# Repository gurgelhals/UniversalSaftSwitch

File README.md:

UniversalSaftSwitch
===========

UniversalSaftSwitch - powers on/off devices using the RS-485 bus

Fuses:
-U lfuse:w:0xde:m -U hfuse:w:0xdf:m -U efuse:w:0xff:m 

project page: https://www.binary-kitchen.de/wiki/doku.php?id=projekte:hausautomatisierung:uss

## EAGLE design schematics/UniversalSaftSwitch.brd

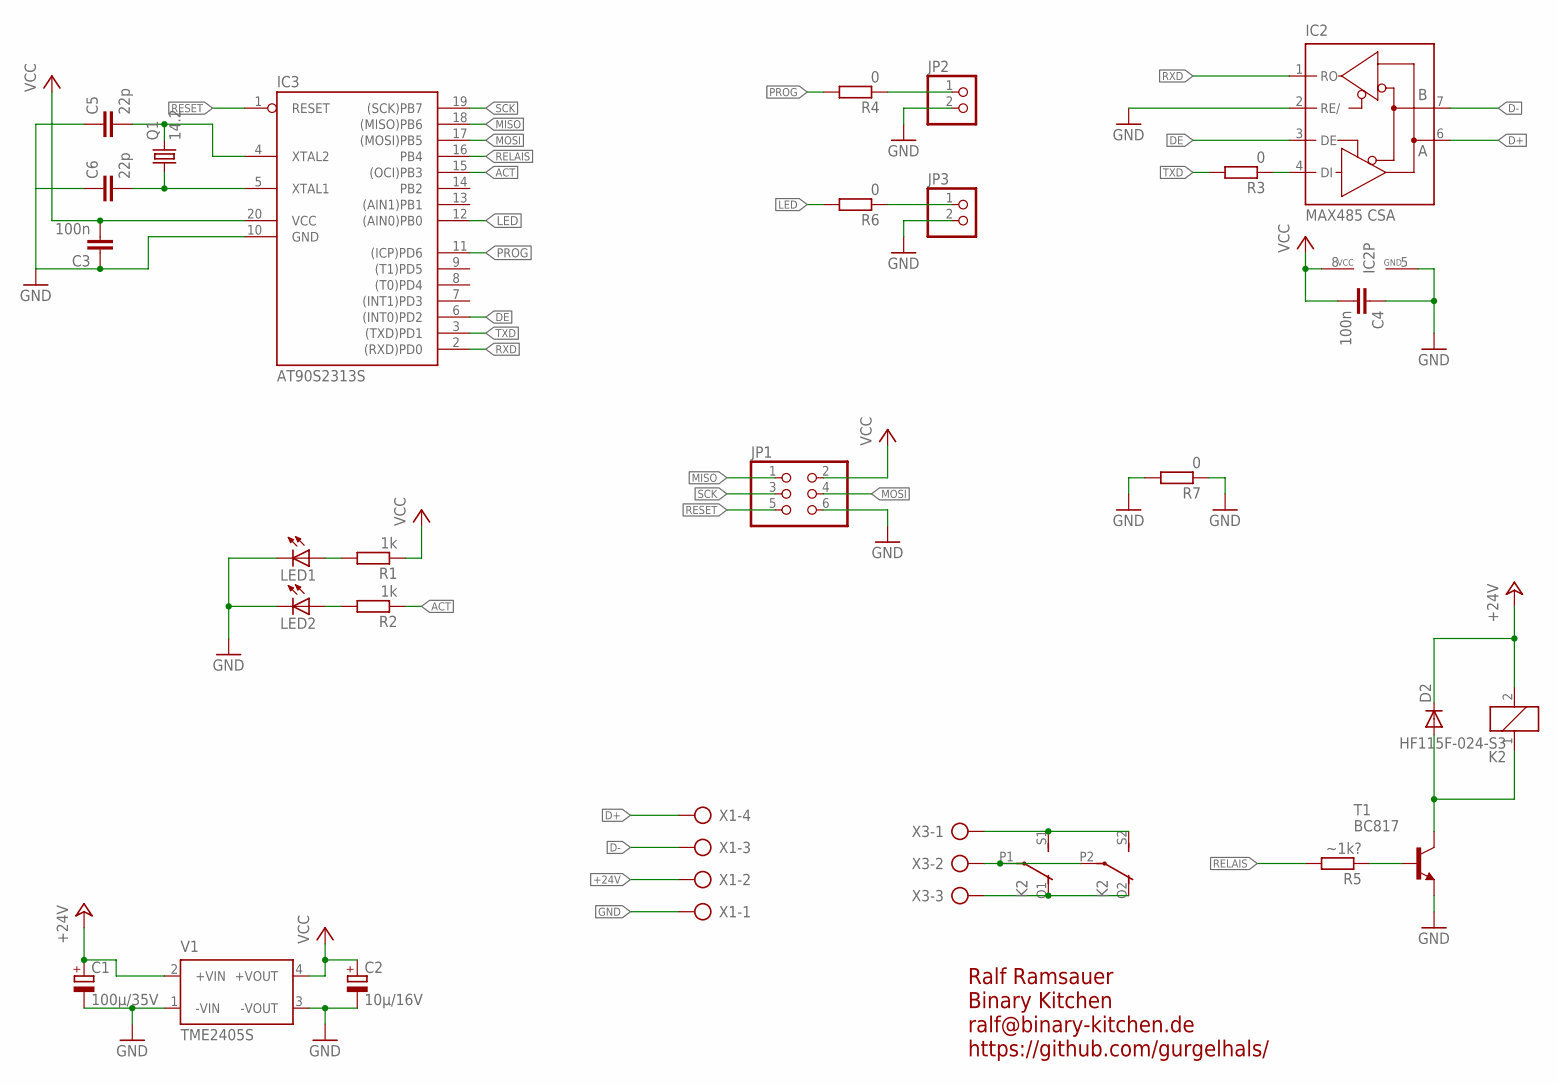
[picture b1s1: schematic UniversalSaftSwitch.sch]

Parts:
C1: 100µ/35V; E3,5-8
C2: 10µ/16V; E2-4
C3, C4: 100n; C0805K
C5, C6: 22p; C0805K
D2: DIODE-MINIMELF; MINIMELF
IC2: MAX485 CSA; SO08
IC3: AT90S2313S; SO20L
JP1: PINHD-2X3; 2X03
JP2, JP3: PINHD-1X2; 1X02
K2: HF115F-024-S3; F4052
LED1, LED2: LED3MM
Q1: 14.2; HC49U-V
R1, R2: 1k; M0805
R3, R4, R6, R7: 0; M0805
R5: ~1k?; M0805
T1: BC817; SOT23-BEC
V1: TME2405S; TME-24V
X1: AK500/4
X3: AK500/3

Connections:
+24V: C1.+, D2.C, K2.2, V1.2 (+VIN), X1.2
ACT: IC3.15 ((OCI)PB3), R2.1
D+: IC2.6 (A), X1.4
D-: IC2.7 (B), X1.3
DE: IC2.3 (DE), IC3.6 ((INT0)PD2)
GND: C1.-, C2.-, C3.1, C4.1, C5.1, C6.1, IC2.2 (RE/), IC2.5 (GND), IC3.10 (GND), JP1.6, JP2.2, JP3.2, LED1.K (C), LED2.K (C), R7.1, R7.2, T1.E, V1.1 (-VIN), V1.3 (-VOUT), X1.1
LED: IC3.12 ((AIN0)PB0), R6.2
MISO: IC3.18 ((MISO)PB6), JP1.1
MOSI: IC3.17 ((MOSI)PB5), JP1.4
unnamed: IC2.4 (DI), R3.1
unnamed: LED1.A, R1.2
unnamed: LED2.A, R2.2
unnamed: K2.S1 (S), K2.S2 (S), X3.1
unnamed: K2.O1 (O), K2.O2 (O), X3.3
unnamed: K2.P1, K2.P2, X3.2
unnamed: C5.2, IC3.4 (XTAL2), Q1.2
unnamed: D2.A, K2.1, T1.C
unnamed: R5.1, T1.B
unnamed: C6.2, IC3.5 (XTAL1), Q1.1
unnamed: JP2.1, R4.1
unnamed: JP3.1, R6.1
PROG: IC3.11 ((ICP)PD6), R4.2
RELAIS: IC3.16 (PB4), R5.2
RESET: IC3.1 (RESET), JP1.5
RXD: IC2.1 (RO), IC3.2 ((RXD)PD0)
SCK: IC3.19 ((SCK)PB7), JP1.3
TXD: IC3.3 ((TXD)PD1), R3.2
VCC: C2.+, C3.2, C4.2, IC2.8 (VCC), IC3.20 (VCC), JP1.2, R1.1, V1.4 (+VOUT)

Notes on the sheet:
Ralf Ramsauer Binary Kitchen ralf@binary-kitchen.de https://github.com/gurgelhals/

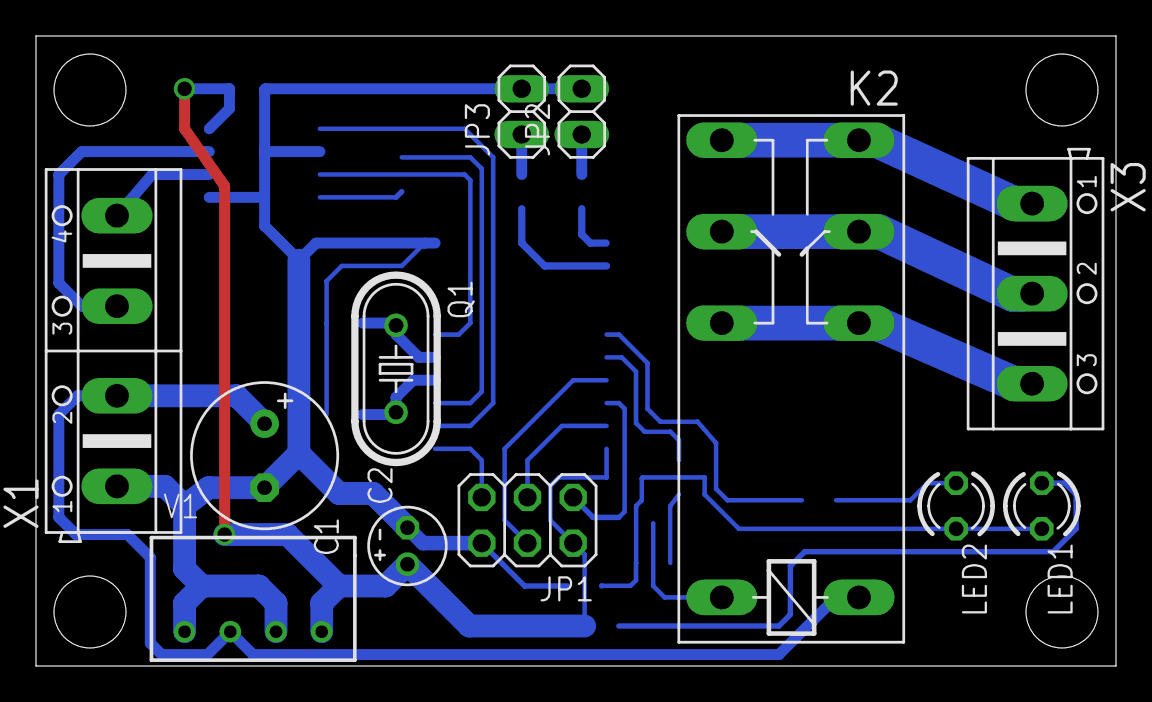
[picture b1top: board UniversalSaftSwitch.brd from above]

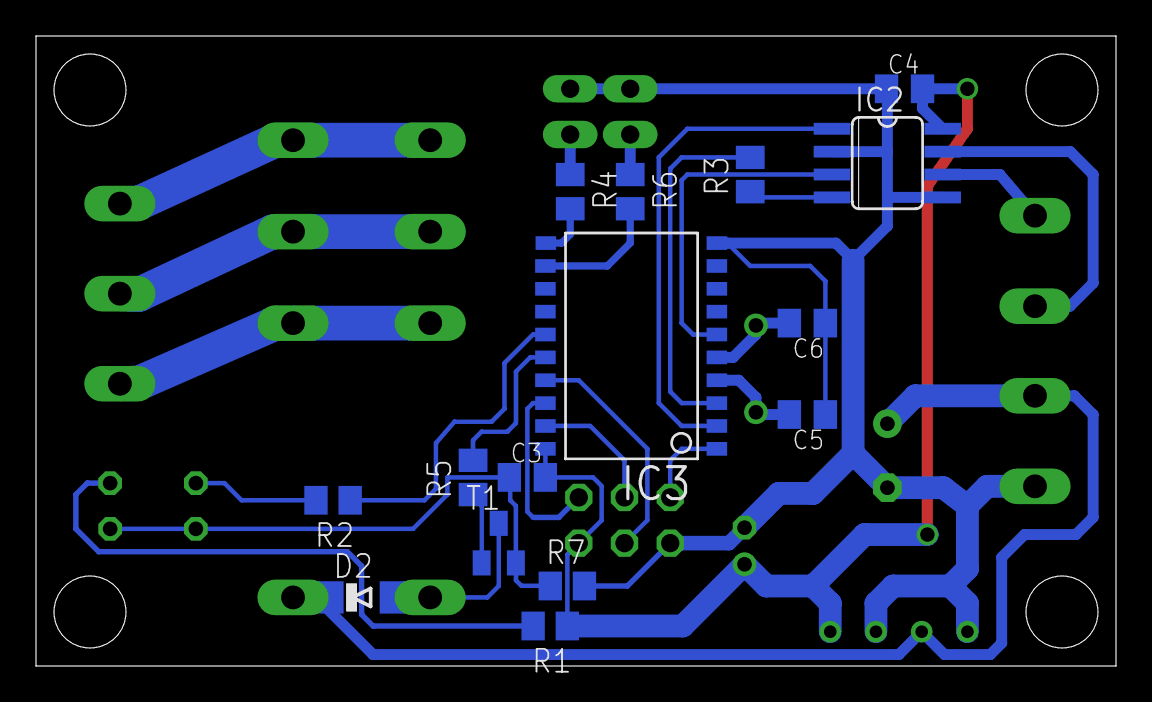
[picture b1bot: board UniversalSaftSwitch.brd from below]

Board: 2 copper layers, 60.0 x 35.0 mm, 27 parts (15 on the bottom side), 28 nets.

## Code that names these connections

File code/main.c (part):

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#include <avr/sleep.h>
#include <string.h>

#define ACT_ON (PORTB |= (1<<PB3))
#define ACT_OFF (PORTB &= ~(1<<PB3))

#define REL_ON (PORTB |= (1<<PB4))
#define REL_OFF (PORTB &= ~(1<<PB4))

#define PROG_ON (!(PIND & (1<<PD6)))

#define DE_RX (PORTD &= ~(1<<PD2))
#define DE_TX (PORTD |= (1<<PD2))

#define TIMER_OFF {\
    TIMSK = 0;\
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    // disable all interrupts
    cli();

    // PB3, PB4 as output
    DDRB = (1<<PB3)|(1<<PB4);

    // PD6 as input + pull up
    DDRD &= ~(1<<PD6);
    PORTD |= (1<<PD6);

    // PD2 (DE) as output and to Recv Mode
    DDRD |= (1<<PD2);
    DE_RX;

    // 115200bps @ 14.7456 MHz
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
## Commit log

2014-05-31 Initial commit, testing code
2014-06-03 New Schematic
2014-06-04 New schematic + pcb
2014-06-05 first testing code, without CRC8 little changes in schematic
2015-02-28 Added CRC8 support
